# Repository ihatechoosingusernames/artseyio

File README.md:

# artseyio
Hardware for an [ARTSEYIO layout](https://artsey.io/) single hand keyboard. The controller is a [CH552G](https://raw.githubusercontent.com/WeActStudio/WeActStudio.CH552CoreBoard/master/Datasheet/CH552DS1_en.PDF) and connects via USB-C.

The firmware requires [SDCC](https://sdcc.sourceforge.net/) and is based on an [excellent project by Wagiminator](https://github.com/wagiminator/CH552-USB-Knob).

The v1.1 layout.

A completed v1.0 board.

### Flashing
To compile the software, install sdcc and python3 and pyusb with pip, following the instructions from the [Wagiminator repo.](https://github.com/wagiminator/CH552-USB-Knob)

To flash, power up the board while shorting the BOOT jumper with tweezers or a piece of solder. Release the short once the device is plugged in, it should be in boot mode. Run `make flash` in the artseyio-firmware directory, and the board should be programmed.

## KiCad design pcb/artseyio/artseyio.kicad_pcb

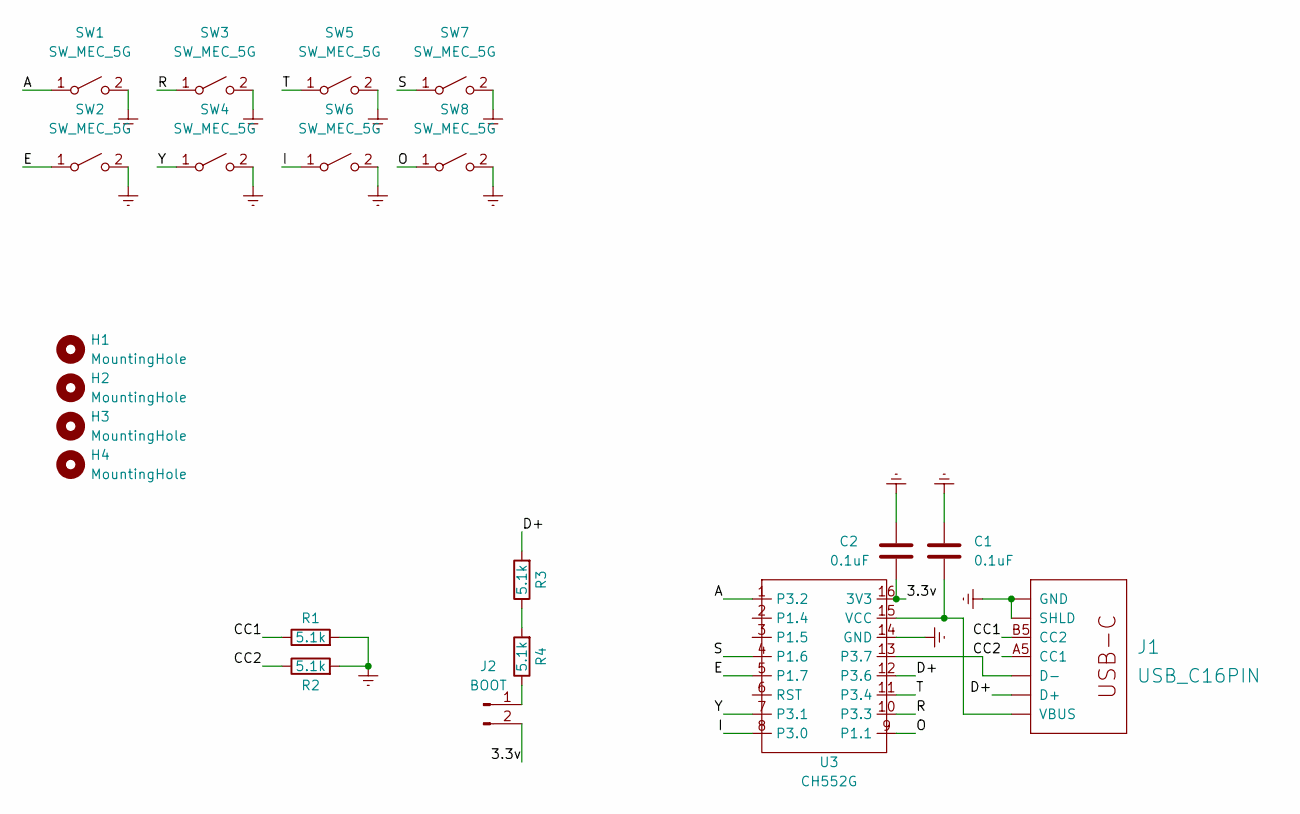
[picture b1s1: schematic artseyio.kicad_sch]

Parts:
C1, C2: 0.1uF; C_0805_2012Metric_Pad1.18x1.45mm_HandSolder
H1, H2, H3, H4: MountingHole; MountingHole_3.2mm_M3
J1: USB_C16PIN; USB-C-COM-15111
J2: BOOT; PinHeader_1x02_P2.54mm_Vertical
R1, R2, R3, R4: 5.1k; R_0805_2012Metric
SW1, SW2, SW3, SW4, SW5, SW6, SW7, SW8: SW_MEC_5G; SW_Cherry_MX_1.00u_PCB
U3: CH552G

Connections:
/3.3v: C2.2, J2.2, U3.16 (3V3)
/A: SW1.1 (A), U3.1 (P3.2)
/CC1: J1.B5 (CC2), R1.1
/CC2: J1.A5 (CC1), R2.1
/D+: J1.A6 (D+), J1.B6 (D+), R3.2, U3.12 (P3.6)
/E: SW2.1 (A), U3.5 (P1.7)
/I: SW6.1 (A), U3.8 (P3.0)
/O: SW8.1 (A), U3.9 (P1.1)
/R: SW3.1 (A), U3.10 (P3.3)
/S: SW7.1 (A), U3.4 (P1.6)
/T: SW5.1 (A), U3.11 (P3.4)
/Y: SW4.1 (A), U3.7 (P3.1)
Earth: C1.1, C2.1, J1.GND, J1.GND2 (GND), J1.SHLD1 (SHLD), J1.SHLD2 (SHLD), J1.SHLD3 (SHLD), J1.SHLD4 (SHLD), J1.SHLD5 (SHLD), J1.SHLD6 (SHLD), J1.SHLD7 (SHLD), J1.SHLD8 (SHLD), R1.2, R2.2, SW1.2 (B), SW2.2 (B), SW3.2 (B), SW4.2 (B), SW5.2 (B), SW6.2 (B), SW7.2 (B), SW8.2 (B), U3.14 (GND)
unnamed: C1.2, J1.VBUS1 (VBUS), J1.VBUS2 (VBUS), U3.15 (VCC)
unnamed: J1.A7 (D-), J1.B7 (D-), U3.13 (P3.7)
unnamed: J2.1, R4.1
unnamed: R3.1, R4.2

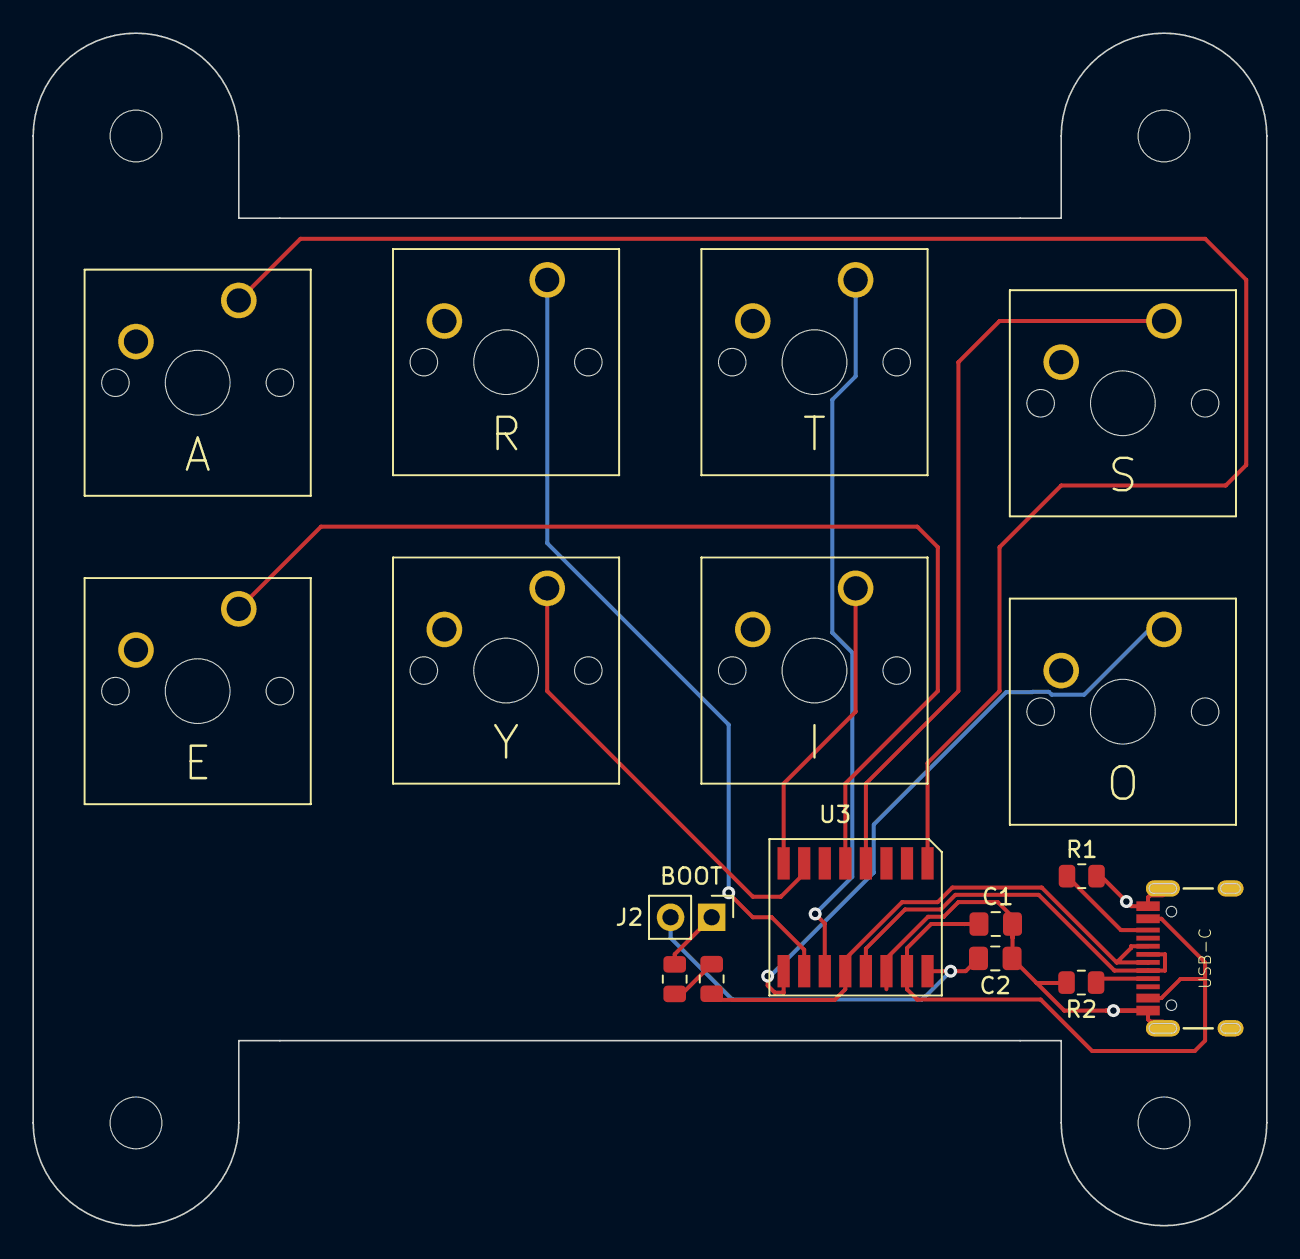
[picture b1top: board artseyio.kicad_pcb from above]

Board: 2 copper layers, 76.2 x 73.7 mm, 21 parts (0 on the bottom side), 17 nets.

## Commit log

2023-02-18 Added hardware design and layout.
2023-02-18 Updated readme with pcb layout.
2023-02-18 Updated readme.
2023-02-18 Updated screenshot.
2023-02-19 Updated schematic to include a CH552 with builtin USB-C port.
2023-02-19 Updated PCB Layout image
2023-02-20 Updated the footprint shape and updated the ESP32 pinout.
2023-02-20 Updated reversed switches, rearranged CH552 to reduce vias and USB track length.
2023-02-20 Added updated gerbers for release v0.2
2023-02-21 Added reset jumpers for CH552G
2023-02-22 Updated to remove RP2040-Zero and ESP32.
2023-02-22 Updated screenshots and README with the final design.
2023-03-14 Added in some missing features to make programming it easier, handle CC lines on USB-C.
2023-03-15 Added firmware adapted from the excellent Wagiminator CH552 projects.
2023-03-19 Fixed hold layer implementation and tap code reset bug.
2023-03-20 Filled out v1.1 design with boot jumper and correct cc line pulldowns.
2023-03-20 Updated firmware with new pinout.
2023-03-20 Fixed image, generated gerbers.
2023-03-20 Updated readme with attribution.
2023-03-20 Added firmware license.
2023-03-20 Updated readme with flashing instructions.
2023-03-20 Updated readme images.
2023-03-22 Slight cleanup.
2023-03-22 Reverted pinout changes to continue 1.0 support.
2023-03-22 Reverted PCB also.
2023-03-23 added the navigation layer.
